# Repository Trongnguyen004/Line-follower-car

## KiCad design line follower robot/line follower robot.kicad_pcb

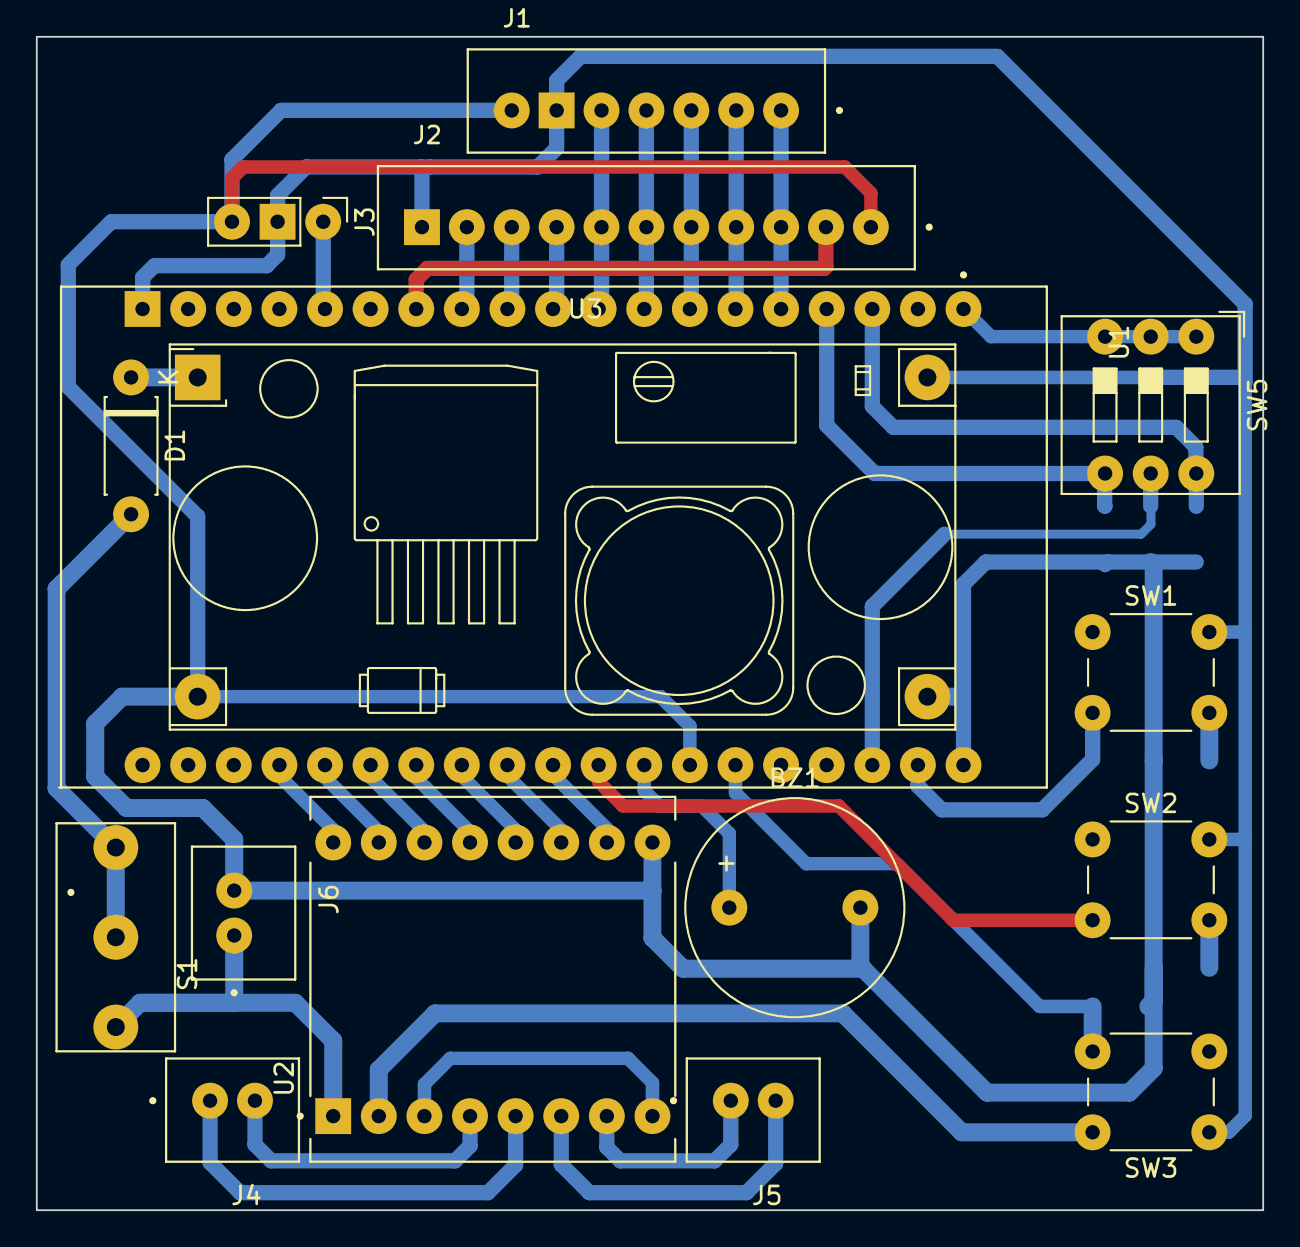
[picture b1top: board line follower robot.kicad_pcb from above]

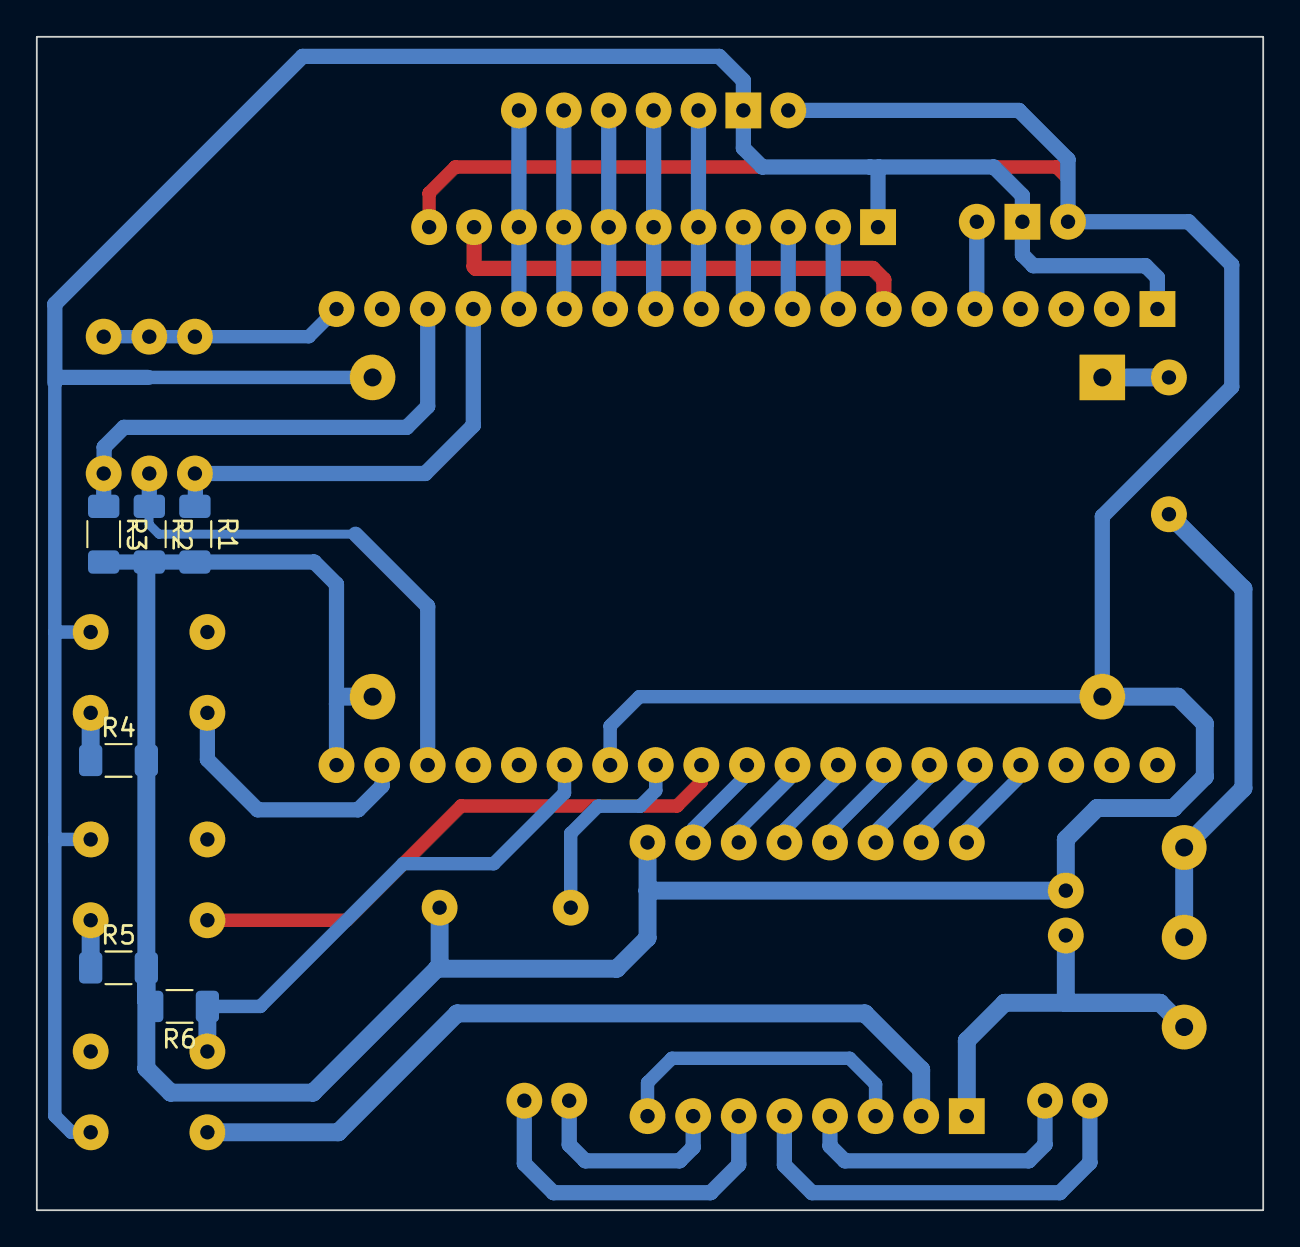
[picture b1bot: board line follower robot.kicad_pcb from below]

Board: 2 copper layers, 68.3 x 65.3 mm, 22 parts (6 on the bottom side), 33 nets.

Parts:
BZ1: Buzzer; Buzzer_12x9.5RM7.6
D1: 1N4007; D_DO-41_SOD81_P7.62mm_Horizontal
J1: JST_B7B-XH-A_LF__SN_
J2: B11B-XH-A_LF__SN_; JST_B11B-XH-A_LF__SN_
J3: Conn_01x03_Pin; PinHeader_1x03_P2.54mm_Vertical
J4, J5: B2B-XH-A_LF__SN_; JST_B2B-XH-A_LF__SN_
J6: connector; JST_B2B-XH-A_LF__SN_
R1, R2, R3, R4, R5, R6: R; R_1206_3216Metric_Pad1.30x1.75mm_HandSolder
S1: công tắc; SW_EG1218
SW1, SW2, SW3: SW_Push; SW_PUSH_6mm_H4.3mm
SW5: SW_DIP_x03; SW_DIP_SPSTx03_Slide_9.78x9.8mm_W7.62mm_P2.54mm
U1: ESP32-DEVKITC-32D; MODULE_ESP32-DEVKITC-32D
U2: TB6612; MODULE_ROB-14450
U3: Module_LM2596; YAAJ_DCDC_StepDown_LM2596

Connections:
+3.3V: SW5.1, SW5.2, SW5.3, U1.J2-1 (3V3)
+5V: J1.6, J2.11, J3.2, SW1.1, SW2.1, SW3.1, U1.J2-19 (EXT_5V), U2.2 (VCC), U3.4 (Vout)
/1: J1.1, J2.3, U1.J2-5 (IO34)
/2: J1.2, J2.4, U1.J2-6 (IO35)
/3: J1.3, J2.5, U1.J2-7 (IO32)
/4: J1.4, J2.6, U1.J2-8 (IO33)
/5: J1.5, J2.7, U1.J2-9 (IO25)
/6: J2.8, U1.J2-10 (IO26)
/7: J2.9, U1.J2-11 (IO27)
/8: J2.10, U1.J2-12 (IO14)
/A: U1.J3-16 (IO15), U2.16 (PWMA)
/A1: U1.J3-14 (IO0), U2.14 (AI1)
/A2: U1.J3-15 (IO2), U2.15 (AI2)
/B: U1.J3-10 (IO5), U2.10 (PWMB)
/B1: U1.J3-12 (IO16), U2.12 (BI1)
/B2: U1.J3-11 (IO17), U2.11 (BI2)
/But1: R4.1, SW1.2, U1.J3-2 (IO23)
/But2: R5.1, SW2.2, U1.J3-9 (IO18)
/But3: R6.1, SW3.2, U1.J3-6 (IO21)
/Buzz: BZ1.1 (-), U1.J3-8 (IO19)
/IR: J2.2, U1.J2-13 (IO12)
/STBY: U1.J3-13 (IO4), U2.13 (STBY)
/SW1: R1.1, SW5.4, U1.J2-4 (SENSOR_VN)
/SW2: R2.1, SW5.5, U1.J3-3 (IO22)
/SW3: R3.1, SW5.6, U1.J2-3 (SENSOR_VP)
GND: BZ1.2 (+), J1.7, J2.1, J3.3, J6.2, R1.2, R2.2, R3.2, R4.2, R5.2, R6.2, U1.J2-14 (GND1), U1.J3-1 (GND3), U1.J3-7 (GND2), U2.3 (GND), U2.8 (GND), U2.9 (GND), U3.2 (GND), U3.3 (GND)
unnamed: D1.2 (A), S1.1, S1.2
unnamed: D1.1 (K), U3.1 (Vin)
unnamed: J4.2, U2.4 (A01)
unnamed: J4.1, U2.5 (A02)
unnamed: J5.1, U2.7 (B01)
unnamed: J5.2, U2.6 (B02)
VCC: J6.1, S1.3, U2.1 (VM)

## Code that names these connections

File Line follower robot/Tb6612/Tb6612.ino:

int But1 = 23;
int But2 = 18;
int But3 = 21;
int Speed = 100;
int SpeedA = 100;
int SpeedB = 100;
int Buzz = 19;
int But3_value, lastBut3_value;
#define STBY   4
#define A   15
#define A1  0
#define A2  2
#define B   5
#define B1  16
#define B2  17

void setup(){
  Serial.begin(115200);
  pinMode(Buzz, OUTPUT);
  digitalWrite(Buzz,HIGH);
  delay(10);
  digitalWrite(Buzz,LOW);
  
  pinMode(STBY, OUTPUT);
//  digitalWrite(STBY,LOW);
  
  pinMode(A1, OUTPUT);
  pinMode(A2, OUTPUT);
  pinMode(A, OUTPUT);

  pinMode(B1, OUTPUT);
  pinMode(B2, OUTPUT);
  pinMode(B, OUTPUT);

  pinMode(But1, INPUT);
  pinMode(But2, INPUT);
  pinMode(But3, INPUT);
}
void For(){
  analogWrite(A,SpeedA);
  digitalWrite(A1,HIGH);
  digitalWrite(A2,LOW);
  analogWrite(B,SpeedB);
  digitalWrite(B1,HIGH);
  digitalWrite(B2,LOW);
}
void Back(){
  analogWrite(A,Speed);
  digitalWrite(A1,LOW);
  digitalWrite(A2,HIGH);
  analogWrite(B,Speed);
  digitalWrite(B1,LOW);
  digitalWrite(B2,HIGH);
}
void Stop(){
  analogWrite(A,0);
  digitalWrite(A1,LOW);
  digitalWrite(A2,LOW);
  analogWrite(B,0);
  digitalWrite(B1,LOW);
  digitalWrite(B2,LOW);
}
void  loop(){
  Run();
  Serial.println(STBY);
  
}
void Run(){
  But3_value = digitalRead(But3);
  if (But3_value != lastBut3_value && But3_value == LOW) {
    if (But3_value == LOW) {
      digitalWrite(STBY, !digitalRead(STBY));
        For();
        delay(5000);
        Stop();
        delay(2000);
//        Back();
//        delay(1000);
//        Stop();
//        delay(2000);
    }
  }
  lastBut3_value = But3_value;
}

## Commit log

2024-02-27 Kicad
